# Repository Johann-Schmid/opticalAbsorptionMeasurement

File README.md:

# opticalAbsorptionMeasurement
You can load the software to the project with this link
<br/><br/>
**[Software](https://github.com/Johann-Schmid/plotLabjack)**
<br/><br/>
Schematic and Board of the Optical Absorptions Measurement Device OAMD

The complete device

The complete device in a case

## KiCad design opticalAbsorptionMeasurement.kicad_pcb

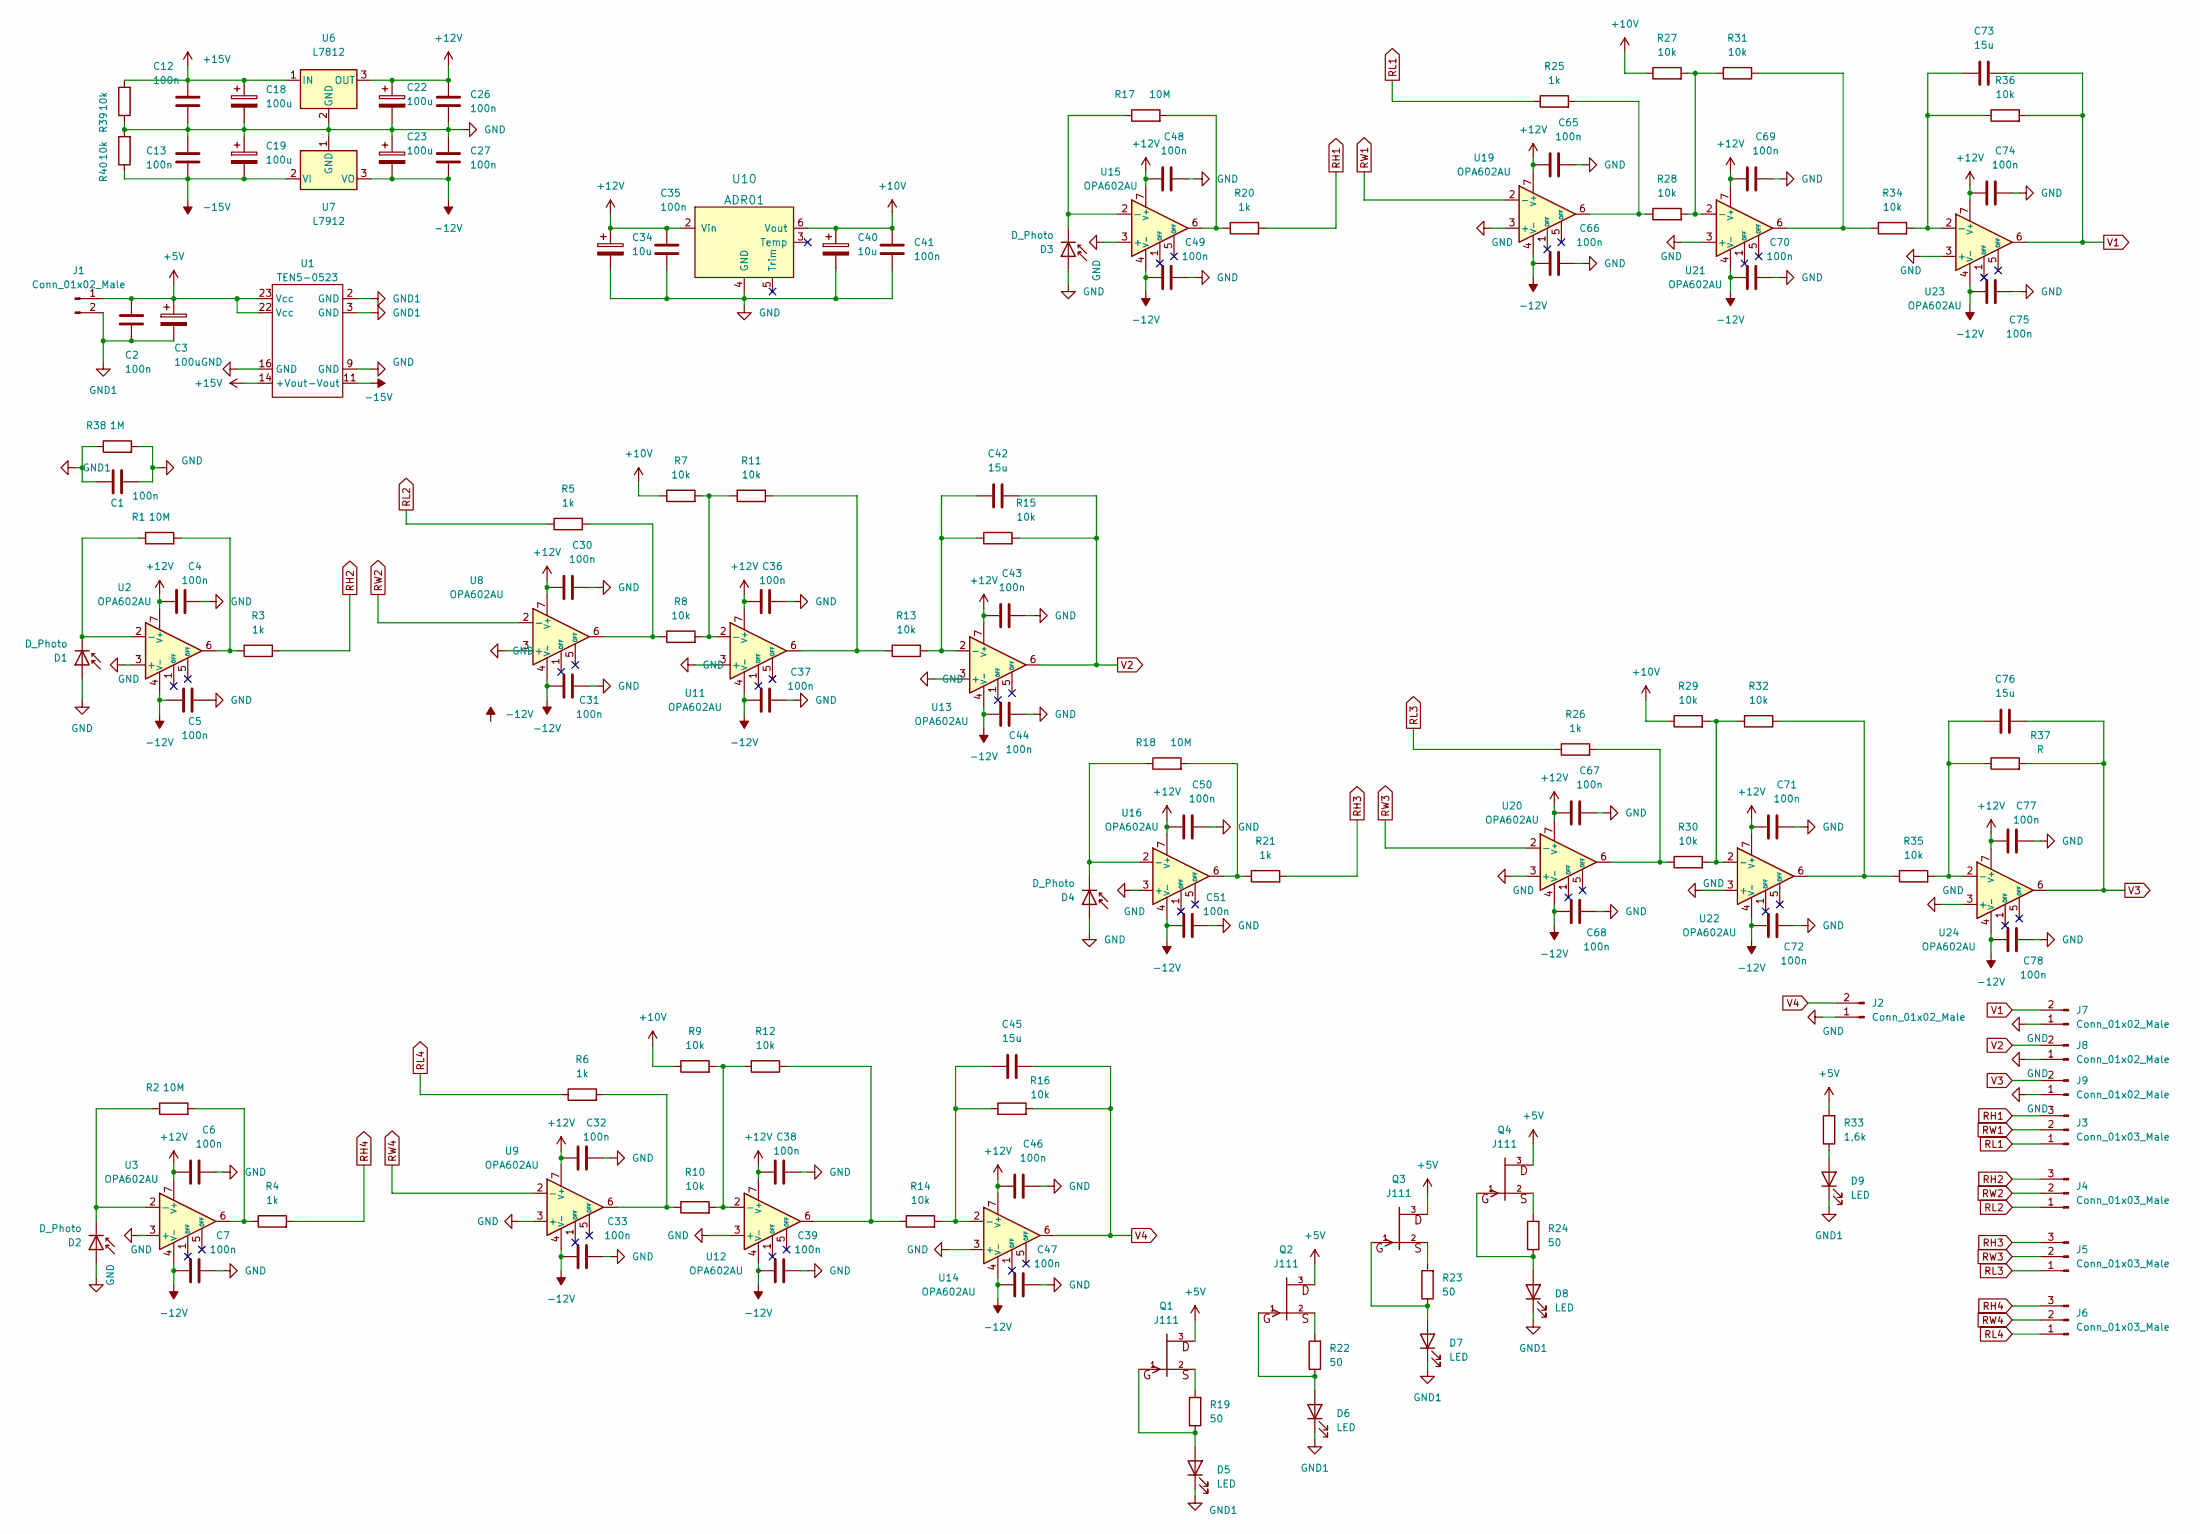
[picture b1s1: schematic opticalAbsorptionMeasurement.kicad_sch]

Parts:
C1, C2, C4, C5, C6, C7, C12, C13, C26, C27, C30, C31, C32, C33, C35, C36, C37, C38, C39, C41, C43, C44, C46, C47, C48, C49, C50, C51, C65, C66, C67, C68, C69, C70, C71, C72, C74, C75, C77, C78: 100n; C_Rect_L7.2mm_W2.5mm_P5.00mm_FKS2_FKP2_MKS2_MKP2
C3, C18, C19, C22, C23: 100u; CP_Radial_D8.0mm_P5.00mm
C34, C40: 10u; CP_Radial_Tantal_D6.0mm_P2.50mm
C42, C45, C73, C76: 15u; CP_Radial_Tantal_D6.0mm_P2.50mm
D1, D2, D3, D4: D_Photo; Osram_SFH205
D5, D6, D7, D8, D9: LED; LED_D5.0mm
J1, J2, J7, J8, J9: Conn_01x02_Male; PinHeader_1x02_P2.54mm_Vertical
J3, J4, J5, J6: Conn_01x03_Male; PinHeader_1x03_P2.54mm_Vertical
Q1, Q2, Q3, Q4: J111; TO92
R1, R2, R17, R18: 10M; R_Axial_DIN0207_L6.3mm_D2.5mm_P10.16mm_Horizontal
R3, R4, R5, R6, R20, R21, R25, R26: 1k; R_Axial_DIN0207_L6.3mm_D2.5mm_P10.16mm_Horizontal
R7, R8, R9, R10, R11, R12, R13, R14, R15, R16, R27, R28, R29, R30, R31, R32, R34, R35, R36, R39, R40: 10k; R_Axial_DIN0207_L6.3mm_D2.5mm_P10.16mm_Horizontal
R19, R22, R23, R24: 50; R_Axial_DIN0207_L6.3mm_D2.5mm_P10.16mm_Horizontal
R33: 1,6k; R_Axial_DIN0207_L6.3mm_D2.5mm_P10.16mm_Horizontal
R37: R; R_Axial_DIN0207_L6.3mm_D2.5mm_P10.16mm_Horizontal
R38: 1M; R_Axial_DIN0207_L6.3mm_D2.5mm_P10.16mm_Horizontal
U1: TEN5-0523
U2, U3, U8, U9, U11, U12, U13, U14, U15, U16, U19, U20, U21, U22, U23, U24: OPA602AU; SO-8_3.9x4.9mm_P1.27mm
U6: L7812; TO-220-3_Vertical
U7: L7912; TO-220-3_Vertical
U10: ADR01; SOIC-8_3.9x4.9mm_P1.27mm

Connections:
+5V: C2.1, C3.1, J1.1, Q1.3, Q2.3, Q3.3, Q4.3, R33.2, U1.22 (Vcc), U1.23 (Vcc)
+10V: C40.1, C41.1, R7.1, R9.1, R27.1, R29.1, U10.6 (Vout)
+12V: C4.1, C6.1, C22.1, C26.1, C30.1, C32.1, C34.1, C35.1, C36.1, C38.1, C43.1, C46.1, C48.1, C50.1, C65.1, C67.1, C69.1, C71.1, C74.1, C77.1, U2.7 (V+), U3.7 (V+), U6.3 (OUT), U8.7 (V+), U9.7 (V+), U10.2 (Vin), U11.7 (V+), U12.7 (V+), U13.7 (V+), U14.7 (V+), U15.7 (V+), U16.7 (V+), U19.7 (V+), U20.7 (V+), U21.7 (V+), U22.7 (V+), U23.7 (V+), U24.7 (V+)
+15V: C12.1, C18.1, R39.2, U1.14 (+Vout), U6.1 (IN)
-12V: C5.1, C7.1, C23.2, C27.2, C31.1, C33.1, C37.1, C39.1, C44.1, C47.1, C49.1, C51.1, C66.1, C68.1, C70.1, C72.1, C75.1, C78.1, U2.4 (V-), U3.4 (V-), U7.3 (VO), U8.4 (V-), U9.4 (V-), U11.4 (V-), U12.4 (V-), U13.4 (V-), U14.4 (V-), U15.4 (V-), U16.4 (V-), U19.4 (V-), U20.4 (V-), U21.4 (V-), U22.4 (V-), U23.4 (V-), U24.4 (V-)
-15V: C13.2, C19.2, R40.1, U1.11 (-Vout), U7.2 (VI)
GND: C1.2, C4.2, C5.2, C6.2, C7.2, C12.2, C13.1, C18.2, C19.1, C22.2, C23.1, C26.2, C27.1, C30.2, C31.2, C32.2, C33.2, C34.2, C35.2, C36.2, C37.2, C38.2, C39.2, C40.2, C41.2, C43.2, C44.2, C46.2, C47.2, C48.2, C49.2, C50.2, C51.2, C65.2, C66.2, C67.2, C68.2, C69.2, C70.2, C71.2, C72.2, C74.2, C75.2, C77.2, C78.2, D1.2 (A), D2.2 (A), D3.2 (A), D4.2 (A), J2.1, J7.1, J8.1, J9.1, R38.2, R39.1, R40.2, U1.9 (GND), U1.16 (GND), U2.3 (+), U3.3 (+), U6.2 (GND), U7.1 (GND), U8.3 (+), U9.3 (+), U10.4 (GND), U11.3 (+), U12.3 (+), U13.3 (+), U14.3 (+), U15.3 (+), U16.3 (+), U19.3 (+), U20.3 (+), U21.3 (+), U22.3 (+), U23.3 (+), U24.3 (+)
GND1: C1.1, C2.2, C3.2, D5.1 (K), D6.1 (K), D7.1 (K), D8.1 (K), D9.1 (K), J1.2, R38.1, U1.2 (GND), U1.3 (GND)
unnamed: D1.1 (K), R1.1, U2.2 (-)
unnamed: D2.1 (K), R2.1, U3.2 (-)
unnamed: D3.1 (K), R17.1, U15.2 (-)
unnamed: D4.1 (K), R18.1, U16.2 (-)
unnamed: D5.2 (A), Q1.1, R19.1
unnamed: D6.2 (A), Q2.1, R22.1
unnamed: D7.2 (A), Q3.1, R23.1
unnamed: D8.2 (A), Q4.1, R24.1
unnamed: D9.2 (A), R33.1
unnamed: Q1.2, R19.2
unnamed: Q2.2, R22.2
unnamed: Q3.2, R23.2
unnamed: Q4.2, R24.2
unnamed: R1.2, R3.1, U2.6
unnamed: R2.2, R4.1, U3.6
unnamed: R5.2, R8.1, U8.6
unnamed: R6.2, R10.1, U9.6
unnamed: R11.1, R13.1, U11.6
unnamed: R12.1, R14.1, U12.6
unnamed: R17.2, R20.1, U15.6
unnamed: R18.2, R21.1, U16.6
unnamed: R25.2, R28.1, U19.6
unnamed: R26.2, R30.1, U20.6
unnamed: R31.1, R34.1, U21.6
unnamed: R32.1, R35.1, U22.6
unnamed: R7.2, R8.2, R11.2, U11.2 (-)
unnamed: R9.2, R10.2, R12.2, U12.2 (-)
unnamed: C42.1, R13.2, R15.1, U13.2 (-)
unnamed: C45.1, R14.2, R16.1, U14.2 (-)
unnamed: R27.2, R28.2, R31.2, U21.2 (-)
unnamed: R29.2, R30.2, R32.2, U22.2 (-)
unnamed: C73.1, R34.2, R36.1, U23.2 (-)
unnamed: C76.1, R35.2, R37.1, U24.2 (-)
RH1: J3.3, R20.2
RH2: J4.3, R3.2
RH3: J5.3, R21.2
RH4: J6.3, R4.2
RL1: J3.1, R25.1
RL2: J4.1, R5.1
RL3: J5.1, R26.1
RL4: J6.1, R6.1
RW1: J3.2, U19.2 (-)
RW2: J4.2, U8.2 (-)
RW3: J5.2, U20.2 (-)
RW4: J6.2, U9.2 (-)
V1: C73.2, J7.2, R36.2, U23.6
V2: C42.2, J8.2, R15.2, U13.6
V3: C76.2, J9.2, R37.2, U24.6
V4: C45.2, J2.2, R16.2, U14.6

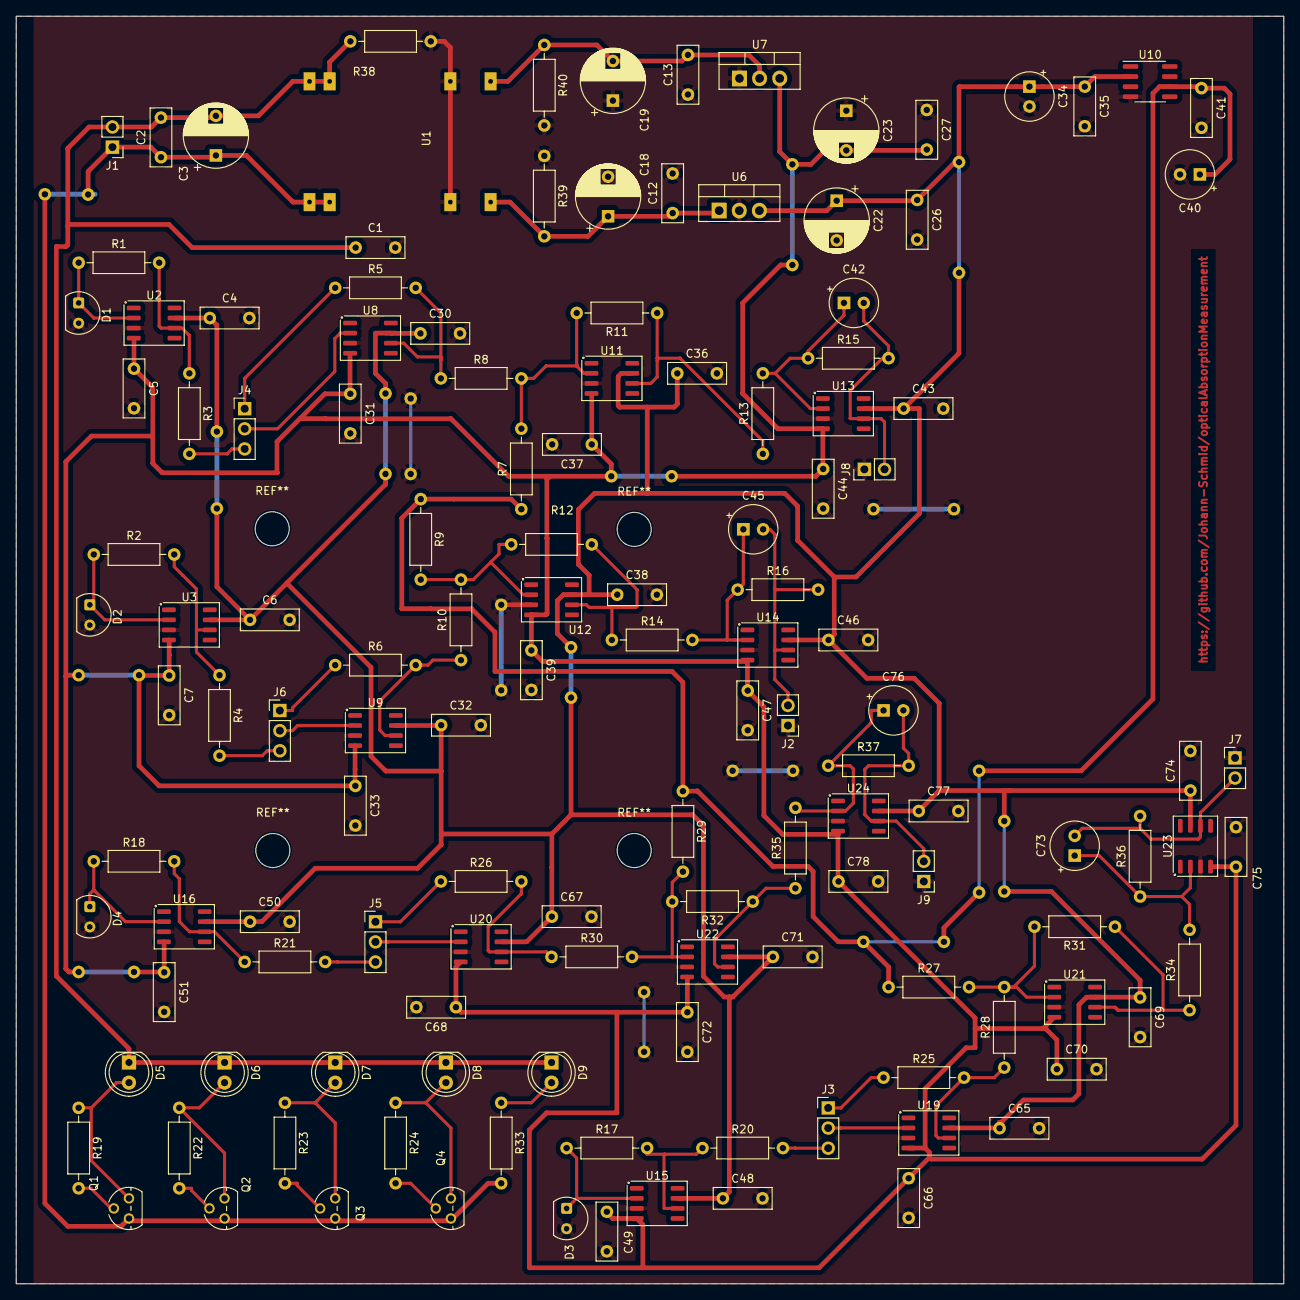
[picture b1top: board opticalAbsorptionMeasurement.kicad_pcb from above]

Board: 2 copper layers, 160.0 x 160.0 mm, 133 parts (0 on the bottom side), 57 nets.

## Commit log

2023-05-11 update resistor
    update resistor
2023-05-11 bom list
2023-05-24 change pin distance TEN5-0523
2023-06-26 Add files via upload
    complete device
2023-10-25 pictures of the device
